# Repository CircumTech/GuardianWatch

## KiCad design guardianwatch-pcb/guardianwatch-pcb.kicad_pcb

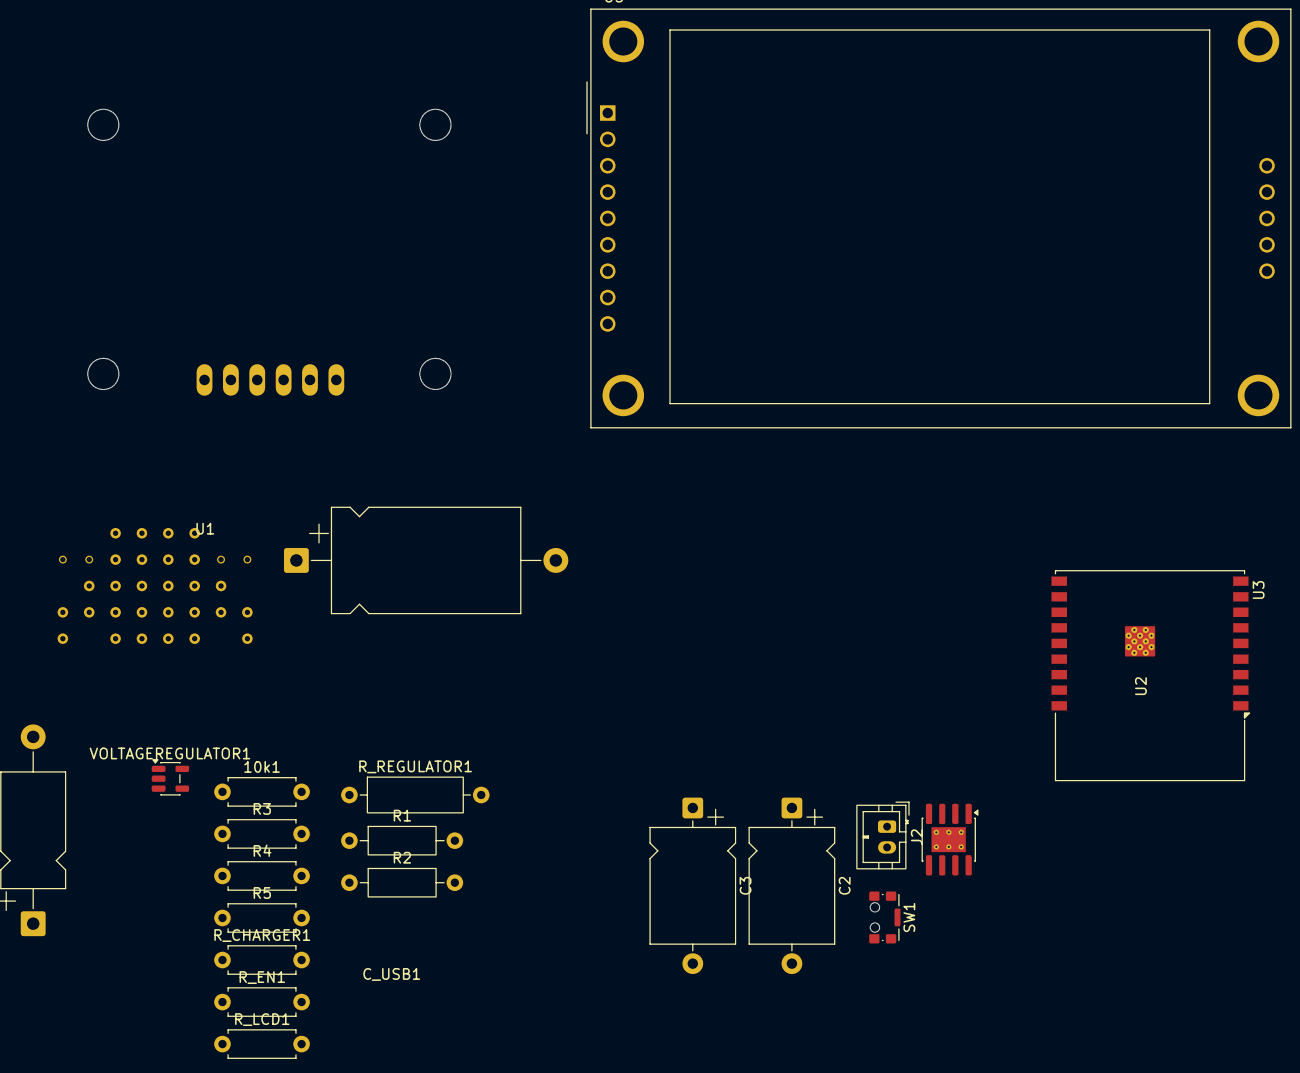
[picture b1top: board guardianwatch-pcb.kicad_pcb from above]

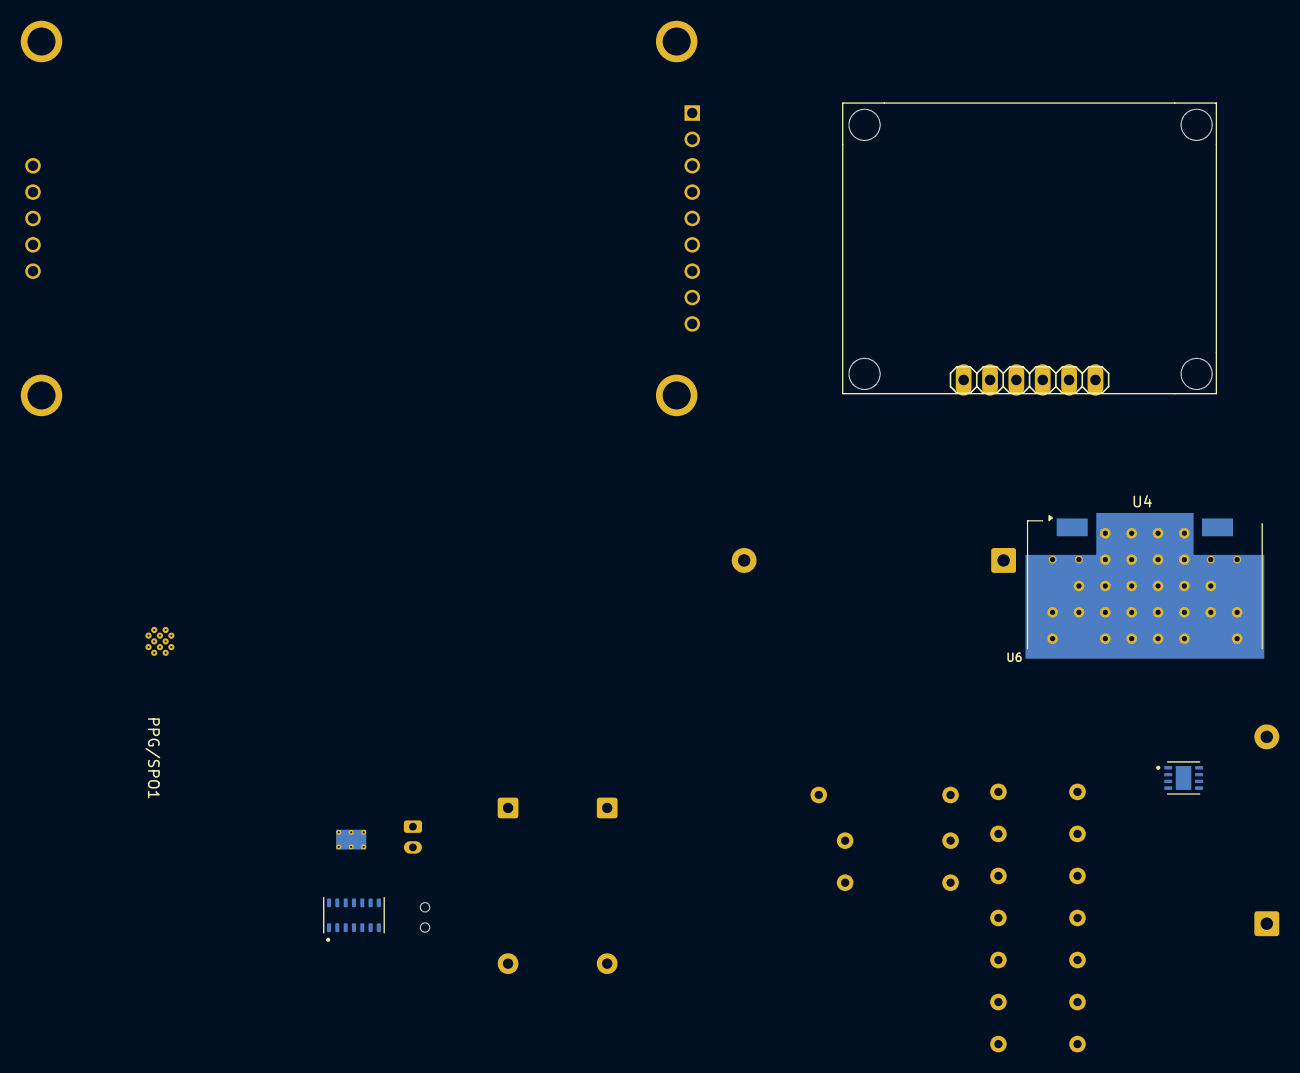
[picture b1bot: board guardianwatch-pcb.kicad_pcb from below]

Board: 2 copper layers, 24 parts (4 on the bottom side), 21 nets, no tracks yet.

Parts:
10k1: R; R_Axial_DIN0207_L6.3mm_D2.5mm_P7.62mm_Horizontal
C1: C_Small; CP_Axial_L11.0mm_D6.0mm_P18.00mm_Horizontal
C2, C3: C_Small; CP_Axial_L11.0mm_D8.0mm_P15.00mm_Horizontal
C_USB1: 1 μF; CP_Axial_L18.0mm_D10.0mm_P25.00mm_Horizontal
J2: BATTERY; JST_PH_B2B-PH-K_1x02_P2.00mm_Vertical
PPG/SPO1: MAX30101EFD_T; PSON80P560X330X165-14N
R1, R2: 100k; R_Axial_DIN0207_L6.3mm_D2.5mm_P10.16mm_Horizontal
R3, R4: 5.1kΩ; R_Axial_DIN0207_L6.3mm_D2.5mm_P7.62mm_Horizontal
R5: 3kΩ; R_Axial_DIN0207_L6.3mm_D2.5mm_P7.62mm_Horizontal
R_CHARGER1: 10kΩ; R_Axial_DIN0207_L6.3mm_D2.5mm_P7.62mm_Horizontal
R_EN1: 10kΩ; R_Axial_DIN0207_L6.3mm_D2.5mm_P7.62mm_Horizontal
R_LCD1: 10kΩ; R_Axial_DIN0207_L6.3mm_D2.5mm_P7.62mm_Horizontal
R_REGULATOR1: 100kΩ; R_Axial_DIN0309_L9.0mm_D3.2mm_P12.70mm_Horizontal
SW1: CK_KMS2xxGP; SW_SPST_CK_KMS2xxGP
U1: MAX30205MTA_; SON65P300X300X80-9N
U2: TP4056-42-ESOP8; SOIC-8-1EP_3.9x4.9mm_P1.27mm_EP2.41x3.3mm_ThermalVias
U3: ESP32-C3-WROOM-02
U4: LPF-B0R3; Mini-Circuits_HZ1198_LandPatternPL-247
U5: CR2013-MI2120
U6: AD8232
VOLTAGEREGULATOR1: ME6211C33M5; SOT-23-5

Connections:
+3.3V: C3.2, PPG/SPO1.11 (VDD), R_EN1.1, R_LCD1.1, U1.8 (VDD), U3.1 (3V3), U5.1 (VCC), U6.VCC (3.3V), VOLTAGEREGULATOR1.5 (V_{OUT})
GND: 10k1.1, C1.1, C2.1, C3.1, C_USB1.2, J2.2, PPG/SPO1.12 (GND), R1.1, R3.2, R4.2, R5.2, SW1.SH (B), U1.4 (GND), U1.6 (A1), U1.7 (A0), U2.3 (GND), U2.9 (EPAD), U3.9 (GND), U3.19 (GND), U4.3 (GND), U4.4 (GND), U4.5 (GND), U4.6 (GND), U5.2 (GND), U6.GND, U6.SDN, VOLTAGEREGULATOR1.2 (V_{SS})
unnamed: 10k1.2, SW1.2
unnamed: C2.2, J2.1, R2.2, R_REGULATOR1.1, SW1.1, U2.5 (BAT), VOLTAGEREGULATOR1.1 (V_{IN})
unnamed: C1.2, R1.2, R2.1
unnamed: PPG/SPO1.2 (SCL), U1.2 (SCL), U3.4 (IO5)
unnamed: PPG/SPO1.3 (SDA), U1.1 (SDA), U3.3 (IO4), U5.7 (SCK)
unnamed: PPG/SPO1.13 (~INT), U3.12 (IO21/TXD)
unnamed: R_CHARGER1.1, U2.8 (CE)
unnamed: R5.1, U2.2 (PROG)
unnamed: R_EN1.2, U3.2 (EN)
unnamed: U3.17 (IO1), U4.2 (OUT)
unnamed: U3.16 (IO2), U5.8 (LED)
unnamed: U3.5 (IO6), U5.6 (MOSI)
unnamed: U3.6 (IO7), U5.3 (~CS)
unnamed: U3.10 (IO10), U5.10 (SD_CS)
unnamed: U3.11 (IO20/RXD), U5.5 (D/~C)
unnamed: U4.1 (IN), U6.OUTPUT
unnamed: R_LCD1.2, U5.4 (RESET)
unnamed: R_REGULATOR1.2, VOLTAGEREGULATOR1.3 (CE)
VBUS: C_USB1.1, R_CHARGER1.2, U2.4 (V_{CC})

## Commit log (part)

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2026-05-30 Guardian Watch Project Initiated
